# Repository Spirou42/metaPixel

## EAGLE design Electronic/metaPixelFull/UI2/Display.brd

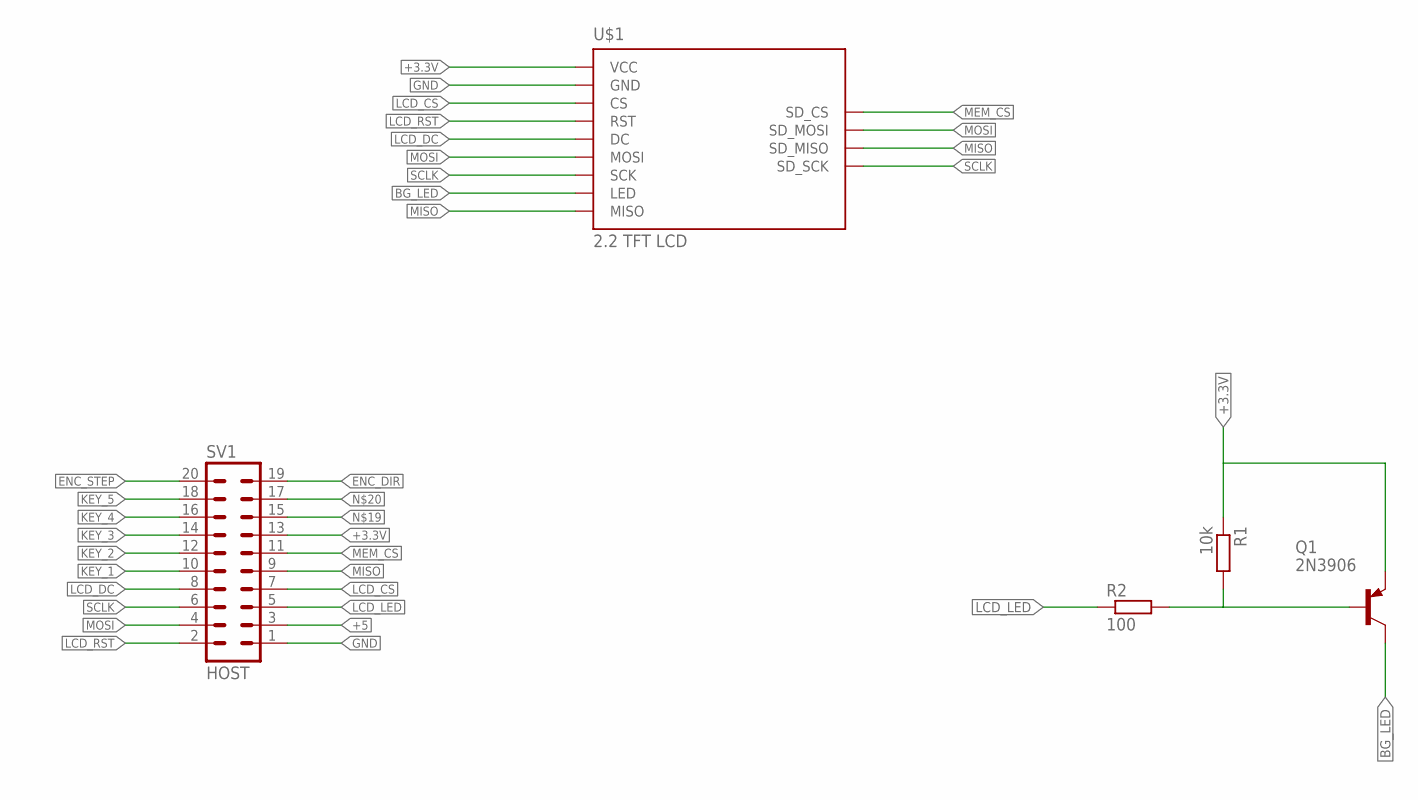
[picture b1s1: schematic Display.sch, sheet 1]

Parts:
Q1: 2N3906; TO92
R1: 10k; 0204/7
R2: 100; 0204/7
SV1: HOST; ML20L
U$1: 2.2_TFT_LCD

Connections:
!LCD_CS: SV1.7, U$1.CS
!LCD_RST: SV1.2, U$1.RST
!MEM_CS: SV1.11, U$1.SD_CS
+3.3V: Q1.3 (E), R1.1, SV1.13, U$1.VCC; also elsewhere on the board
+5: SV1.3
BG_LED: Q1.1 (C), U$1.LED
ENC_DIR: SV1.19; also elsewhere on the board
ENC_STEP: SV1.20; also elsewhere on the board
GND: SV1.1, U$1.GND; also elsewhere on the board
KEY_1: SV1.10; also elsewhere on the board
KEY_2: SV1.12; also elsewhere on the board
KEY_3: SV1.14; also elsewhere on the board
KEY_4: SV1.16; also elsewhere on the board
KEY_5: SV1.18; also elsewhere on the board
LCD_DC: SV1.8, U$1.DC
LCD_LED: R2.1, SV1.5
MISO: SV1.9, U$1.MISO, U$1.SD_MISO
MOSI: SV1.4, U$1.MOSI, U$1.SD_MOSI
unnamed: Q1.2 (B), R1.2, R2.2
SCLK: SV1.6, U$1.SCK, U$1.SD_SCK

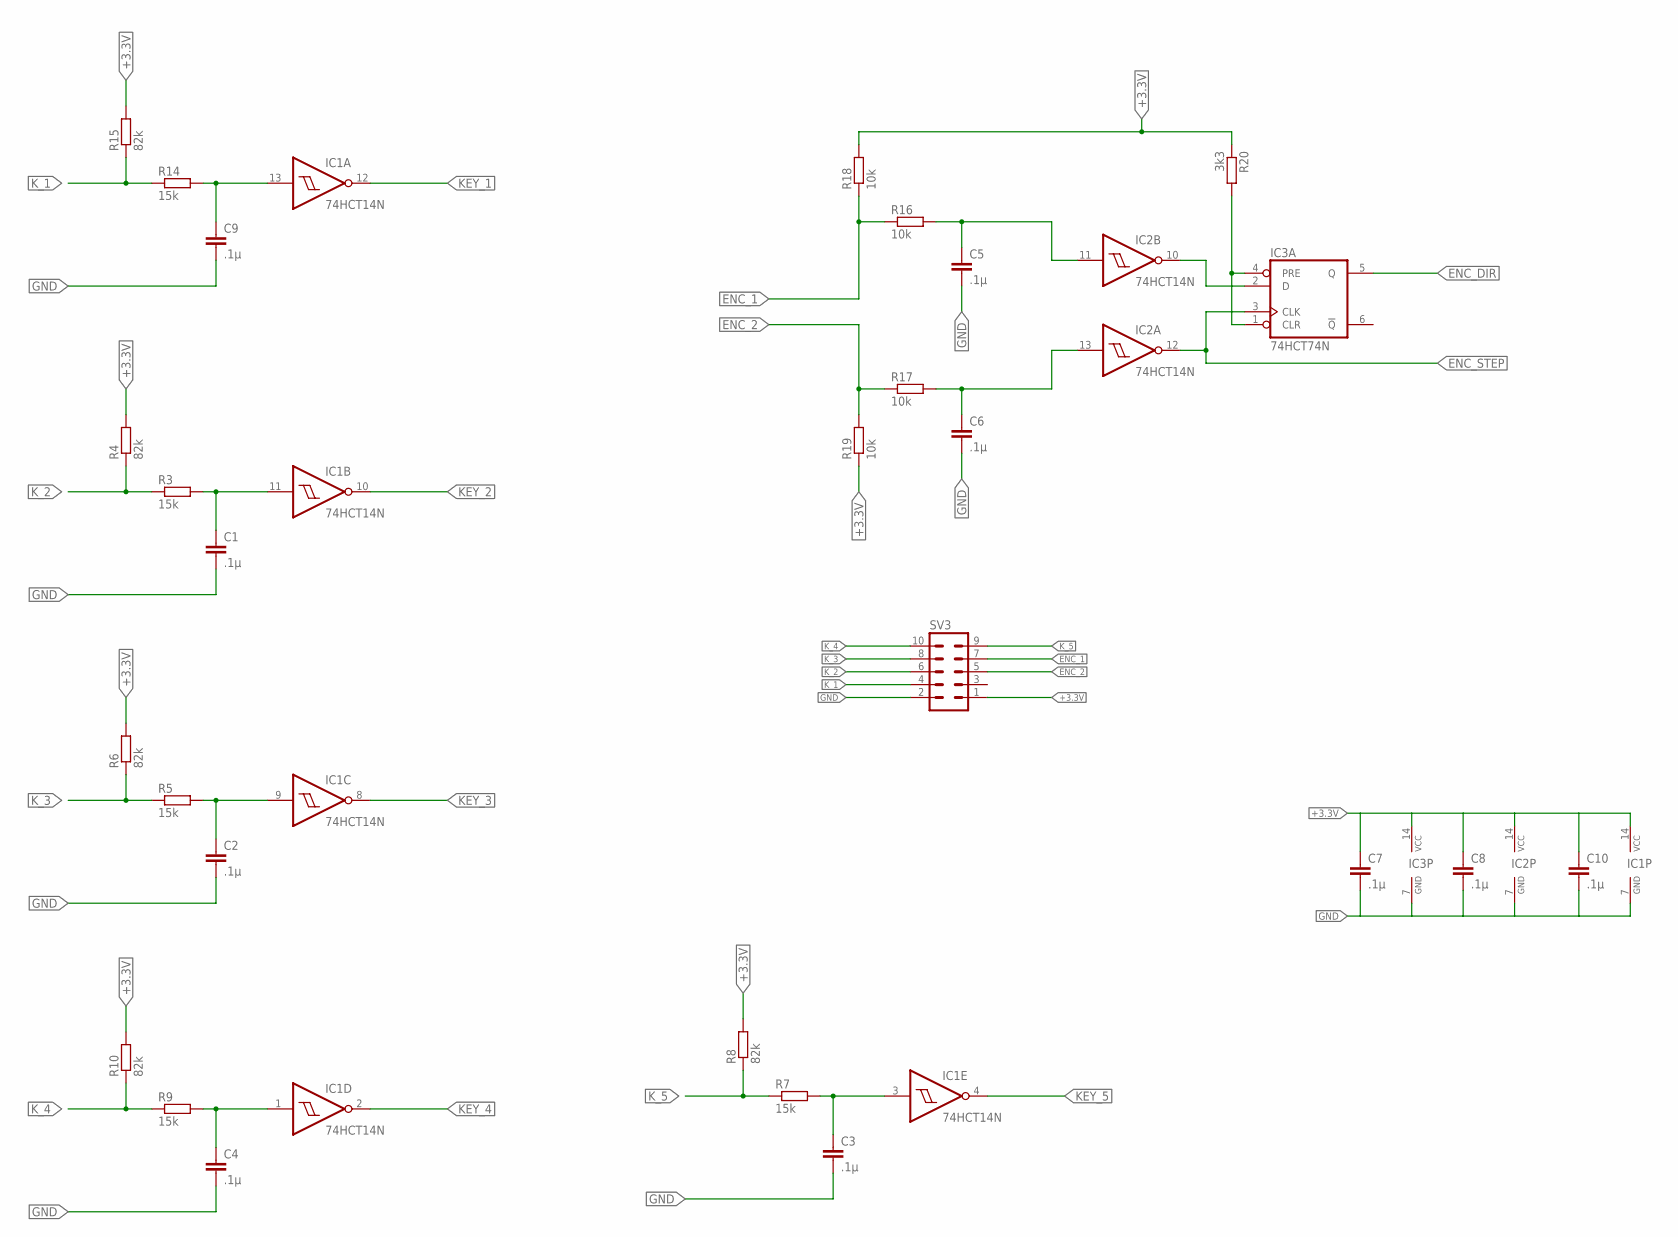
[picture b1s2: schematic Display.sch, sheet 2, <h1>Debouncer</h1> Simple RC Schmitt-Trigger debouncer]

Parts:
C1, C2, C3, C4, C5, C6, C7, C8, C9, C10: .1µ; C025-024X044
IC1, IC2: 74HCT14N; DIL14
IC3: 74HCT74N; DIL14
R3, R5, R7, R9, R14: 15k; 0204/7
R4, R6, R8, R10, R15: 82k; 0204/7
R16, R17, R18, R19: 10k; 0204/7
R20: 3k3; 0204/7
SV3: ML10L

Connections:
+3.3V: C7.1, C8.1, C10.1, IC1.14 (VCC), IC2.14 (VCC), IC3.14 (VCC), R4.2, R6.2, R8.2, R10.2, R15.2, R18.2, R19.1, R20.1, SV3.1; also elsewhere on the board
ENC1: C5.1, IC2.11 (I), R16.2
ENC2: C6.1, IC2.13 (I), R17.2
ENC_1: R16.1, R18.1, SV3.7
ENC_2: R17.1, R19.2, SV3.5
ENC_DIR: IC3.5 (Q); also elsewhere on the board
ENC_STEP: IC2.12 (O), IC3.3 (CLK); also elsewhere on the board
GND: C1.2, C2.2, C3.2, C4.2, C5.2, C6.2, C7.2, C8.2, C9.2, C10.2, IC1.7 (GND), IC2.7 (GND), IC3.7 (GND), SV3.2; also elsewhere on the board
K1: C9.1, IC1.13 (I), R14.2
K2: C1.1, IC1.11 (I), R3.2
K3: C2.1, IC1.9 (I), R5.2
K4: C3.1, IC1.3 (I), R7.2
K5: C4.1, IC1.1 (I), R9.2
KEY_1: IC1.12 (O); also elsewhere on the board
KEY_2: IC1.10 (O); also elsewhere on the board
KEY_3: IC1.8 (O); also elsewhere on the board
KEY_4: IC1.2 (O); also elsewhere on the board
KEY_5: IC1.4 (O); also elsewhere on the board
K_1: R14.1, R15.1, SV3.4
K_2: R3.1, R4.1, SV3.6
K_3: R5.1, R6.1, SV3.8
K_4: R9.1, R10.1, SV3.10
K_5: R7.1, R8.1, SV3.9
unnamed: IC2.10 (O), IC3.2 (D)
unnamed: IC3.1 (CLR), IC3.4 (PRE), R20.2

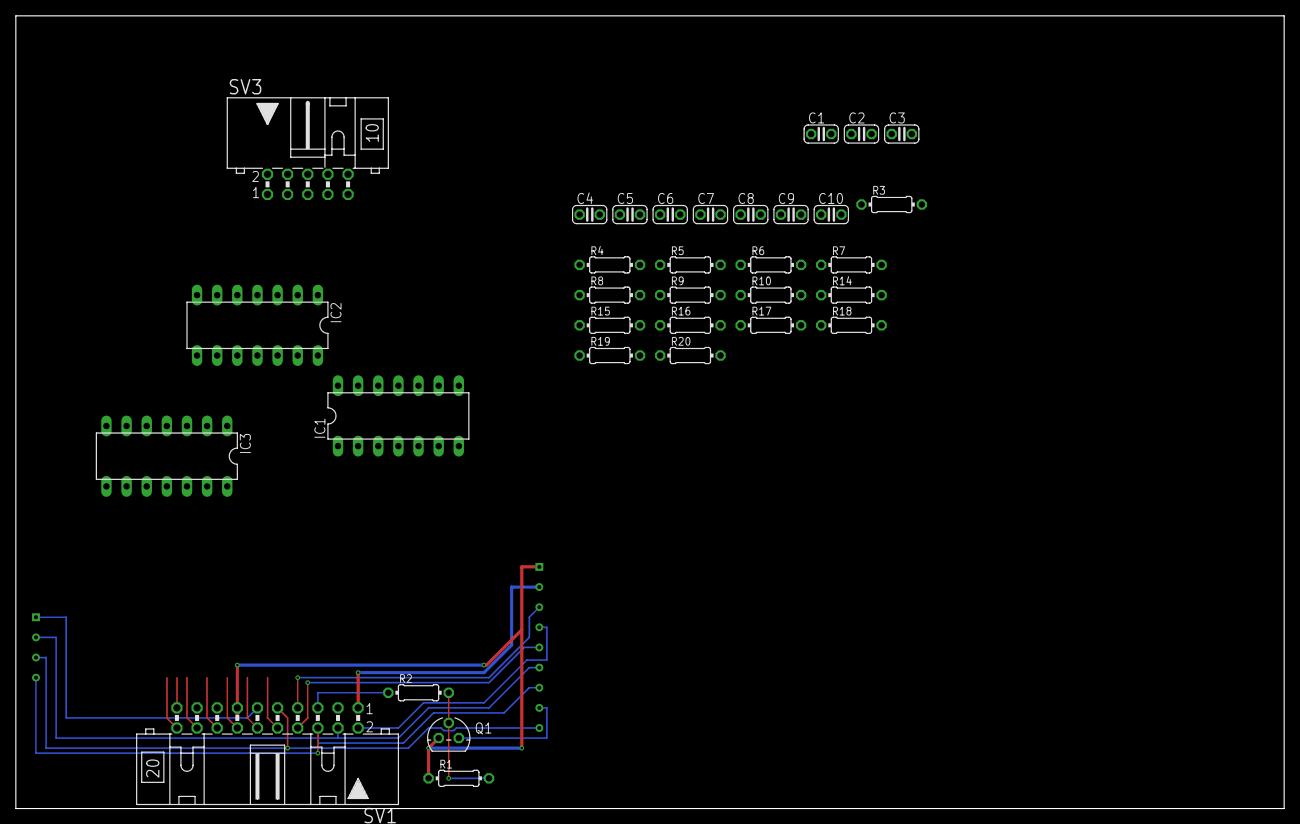
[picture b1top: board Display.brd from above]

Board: 2 copper layers, 160.0 x 100.0 mm, 34 parts (1 on the bottom side), 35 nets.
